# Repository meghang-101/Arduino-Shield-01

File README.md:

# Arduino-Shield-01
Shields are boards that can be plugged on top of the Arduino PCB extending its capabilities.

Most shields are already made and are available in the market for a cheap price.

Some electronics enthusiasts may consider Designing their own custom made Shields which are able to perform simple tasks.

The main reason why custom shields are in high demand is that the user does not need to make electronic connections using a breadboard or a solderable perf-board. The connections are premade, the user has to only place the sensors or actuators in the right place, upload a code to the arduino, place the arduino on top of the shield, and you are good to go.

This custom made arduino shield expects an ARDUINO MEGA to be connected. The connections to the following are made:

Generic 5V RELAYS (x4)

HC05 (bluetooth module)

Serial Communication Ports (TX/RX)

PS2 Reciever

Servo Motors (x3)

Rotary Encoder

Ultrasonic Sensors (x2)

LDR (Light Sensor)

MPU9250 (consists of ACCELEROMETER, GYROMETER, MAGNETOMETER)

MDD10a (Dual H-bridge motor driver)

******######VIEW THE EAGLE_file.brd USING EAGLECAD ONLY######******

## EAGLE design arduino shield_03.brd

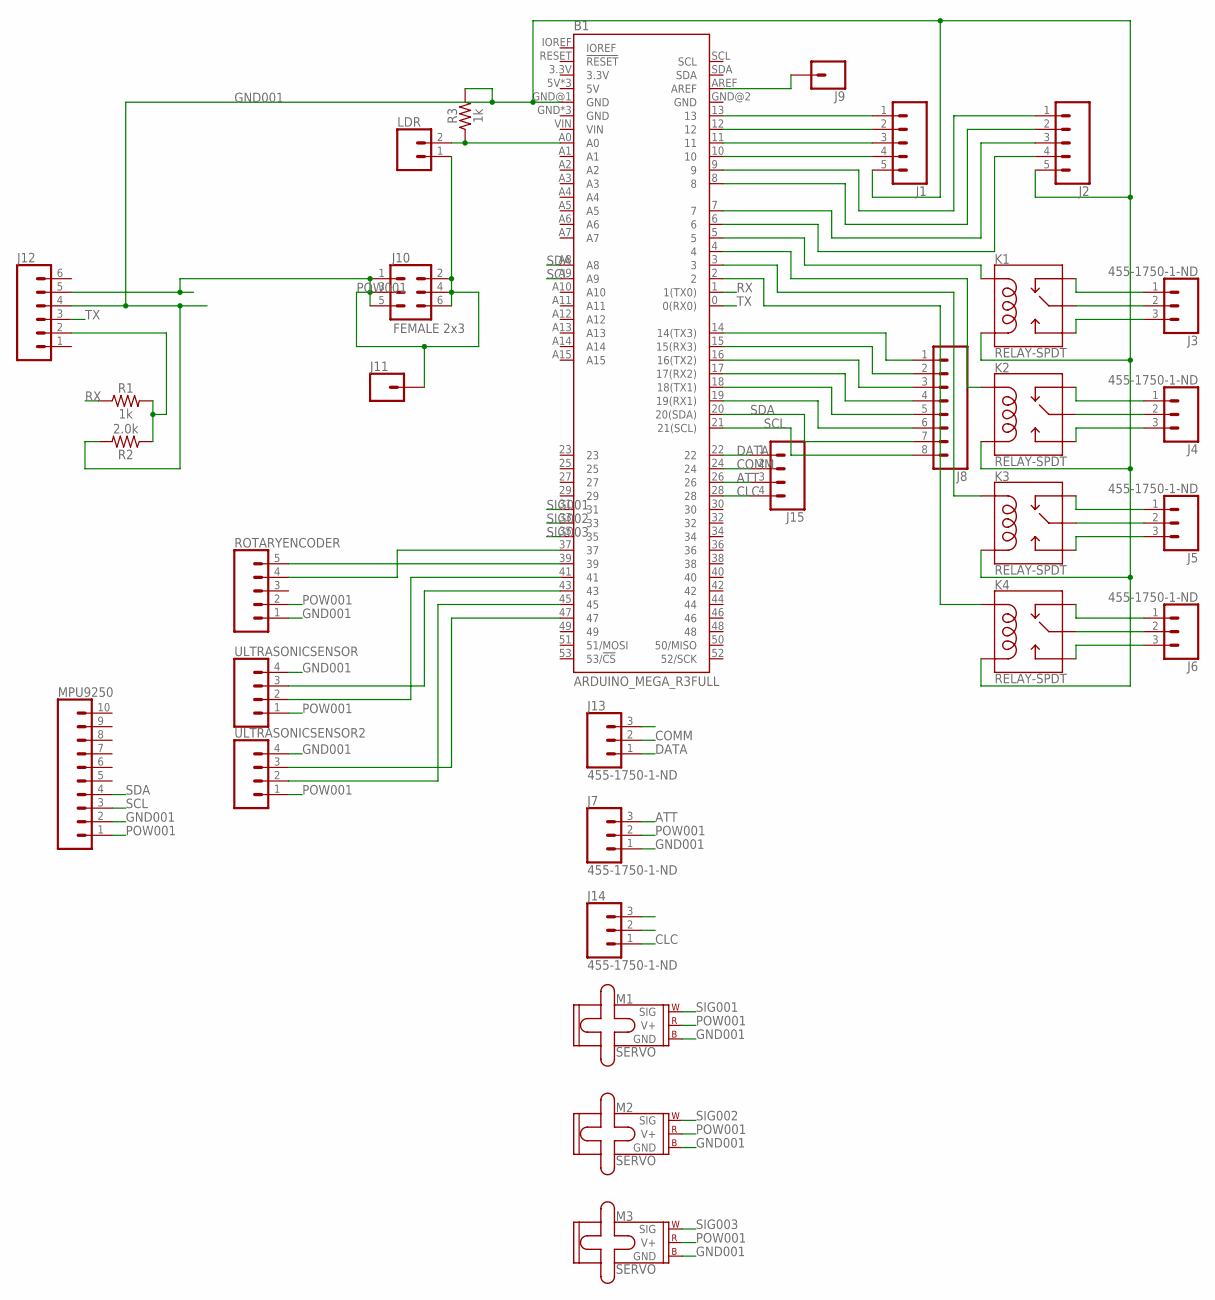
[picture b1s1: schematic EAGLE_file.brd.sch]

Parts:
B1: ARDUINO_MEGA_R3FULL; ARDUINO_MEGA_NO_SILK
J1, J2: CONN_05; 1X05
J3, J4, J5, J6, J7, J13, J14: 455-1750-1-ND; 1X03
J8: CONN_08"; 1X08
J9, J11: CONN_01; 1X01
J10: FEMALE 2x3; 2X3
J12: CONN_06SILK_FEMALE_PTH; 1X06
J15: CONN_04PTH; 1X04
K1, K2, K3, K4: RELAY-SPDT; RELAY_G5LE
LDR: CONN_02; 1X02
M1, M2, M3: SERVO; 1X03
MPU9250: CONN_10"; 1X10
R1, R3: 1k; 0402-TIGHT
R2: 2.0k; 0603
ROTARYENCODER: CONN_05; 1X05
ULTRASONICSENSOR, ULTRASONICSENSOR2: CONN_04PTH; 1X04

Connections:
ATT: B1.26, J7.3, J15.3
CLC: B1.28, J14.1, J15.4
COMM: B1.24, J13.2, J15.2
DATA: B1.22, J13.1, J15.1
GND001: B1.GND@1 (GND), J1.5, J2.5, J7.1, J12.4, K1.5 (COIL2), K2.5 (COIL2), K3.5 (COIL2), K4.5 (COIL2), M1.3 (GND), M2.3 (GND), M3.3 (GND), MPU9250.2, R2.2, R3.2, ROTARYENCODER.1, ULTRASONICSENSOR.4, ULTRASONICSENSOR2.4
unnamed: B1.13, J1.1
unnamed: B1.12, J1.2
unnamed: B1.11, J1.3
unnamed: B1.10, J1.4
unnamed: B1.9, J2.1
unnamed: B1.8, J2.2
unnamed: B1.7, J2.3
unnamed: B1.6, J2.4
unnamed: J12.2, R1.2, R2.1
unnamed: B1.5, K1.2 (COIL1)
unnamed: B1.4, K2.2 (COIL1)
unnamed: J3.1, K1.4 (NC)
unnamed: B1.3, K3.2 (COIL1)
unnamed: B1.2, K4.2 (COIL1)
unnamed: J3.3, K1.3 (NO)
unnamed: J3.2, K1.1 (MAIN)
unnamed: J4.1, K2.4 (NC)
unnamed: J4.3, K2.3 (NO)
unnamed: J4.2, K2.1 (MAIN)
unnamed: J5.1, K3.4 (NC)
unnamed: J5.3, K3.3 (NO)
unnamed: J5.2, K3.1 (MAIN)
unnamed: J6.1, K4.4 (NC)
unnamed: J6.3, K4.3 (NO)
unnamed: J6.2, K4.1 (MAIN)
unnamed: B1.39, ROTARYENCODER.5
unnamed: B1.37, ROTARYENCODER.4
unnamed: B1.41, ULTRASONICSENSOR.2
unnamed: B1.43, ULTRASONICSENSOR.3
unnamed: B1.AREF, J9.1
unnamed: B1.14 (14(TX3)), J8.1
unnamed: B1.15 (15(RX3)), J8.2
unnamed: B1.16 (16(TX2)), J8.3
unnamed: B1.17 (17(RX2)), J8.4
unnamed: B1.18 (18(TX1)), J8.5
unnamed: B1.19 (19(RX1)), J8.6
unnamed: B1.A0, LDR.2, R3.1
unnamed: B1.45, ULTRASONICSENSOR2.2
unnamed: B1.47, ULTRASONICSENSOR2.3
POW001: J7.2, J10.1, J10.2, J10.3, J10.4, J10.5, J10.6, J11.1, J12.5, LDR.1, M1.2 (V+), M2.2 (V+), M3.2 (V+), MPU9250.1, ROTARYENCODER.2, ULTRASONICSENSOR.1, ULTRASONICSENSOR2.1
RX: B1.1 (1(TX0)), R1.1
SCL: B1.21 (21(SCL)), B1.A9, J8.8, MPU9250.3
SDA: B1.20 (20(SDA)), B1.A8, J8.7, MPU9250.4
SIG001: B1.31, M1.1 (SIG)
SIG002: B1.33, M2.1 (SIG)
SIG003: B1.35, M3.1 (SIG)
TX: B1.0 (0(RX0)), J12.3

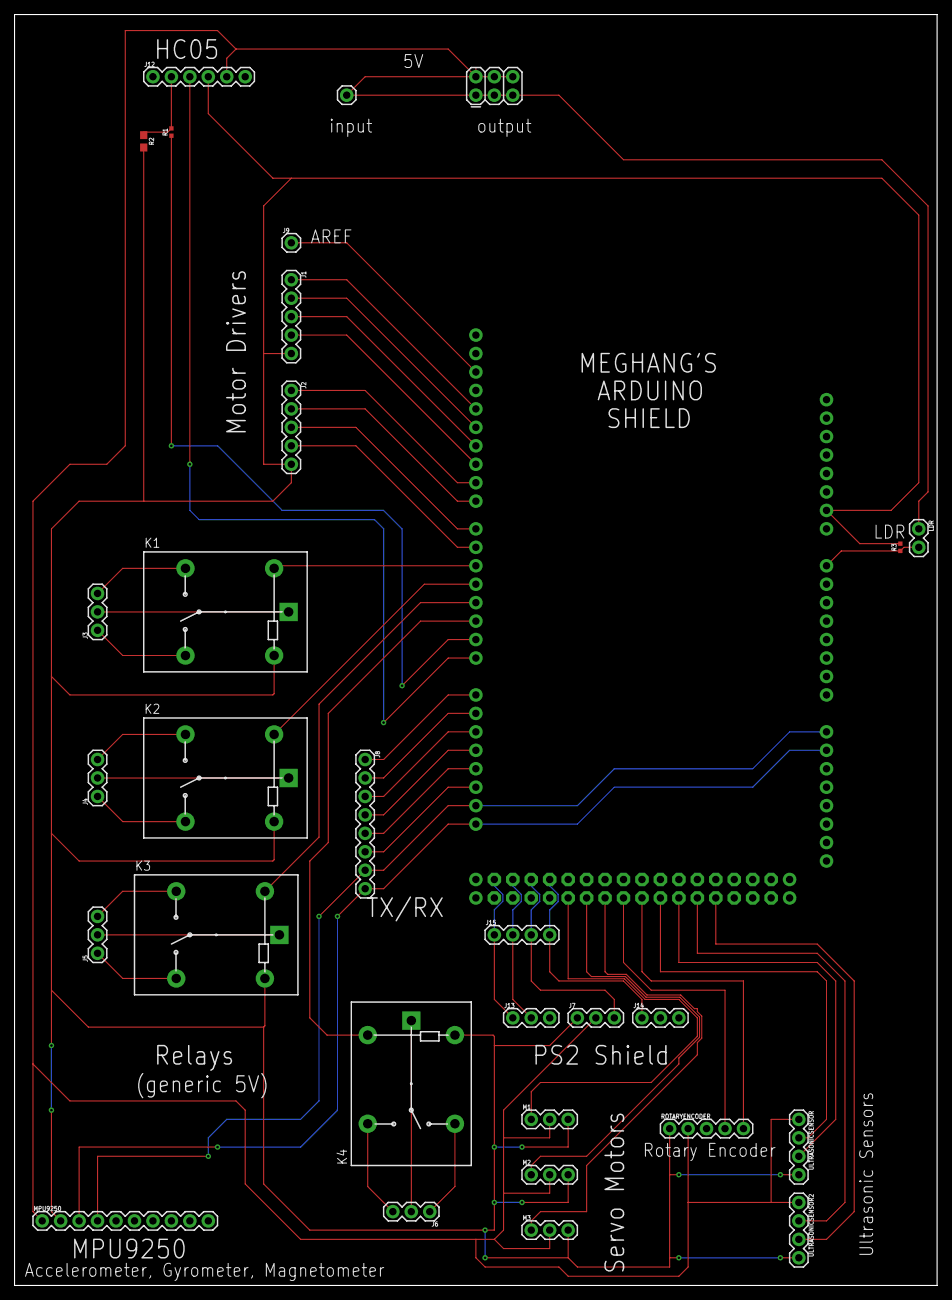
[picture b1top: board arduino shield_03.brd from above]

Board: 2 copper layers, 127.0 x 174.9 mm, 31 parts (1 on the bottom side), 52 nets.

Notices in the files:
parts and their libraries:
SparkFun-Boards: Licensing: Creative Commons ShareAlike 4.0 International - https://creativecommons.org/licenses/by-sa/4.0
